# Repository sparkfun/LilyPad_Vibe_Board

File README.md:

LilyPad Vibe Board
=================

[*SparkFun LilyPad Vibe Board (DEV-11008)*](https://www.sparkfun.com/products/11008)

Apply 5V and be shaken by this small, but powerful vibration motor. Works great as an physical indicator without notifying anyone but the wearer. This version uses a surface mount motor which is less likely to be damaged during use. When using with a 3.3V LilyPad Arduino, make sure to use a [transistor](https://www.sparkfun.com/products/11214) in order to source enough current.

Repository Contents
-------------------

* **/Firmware** - Arduino example code
* **/Hardware** - All Eagle design files (.brd, .sch)
* **/Production** - Test bed files and production panel files

Documentation
--------------

* **[LilyPad Vibe Board Hookup Guide](https://learn.sparkfun.com/tutorials/lilypad-vibe-board-hookup-guide)** - The LilyPad Vibe Board is a small vibration motor that can be sewn into projects with conductive thread and controlled by a LilyPad Arduino. The board can be used as a physical indicator on clothing and costumes for haptic feedback.
* **[LilyPad Development Board Activity Guide: Thermal Alert Project](https://learn.sparkfun.com/tutorials/lilypad-development-board-activity-guide/11-thermal-alert-project)** - Example code using LilyPad Temperature Sensor to trigger the LilyPad Vibe Board when a certain temperature is reached.

License Information
-------------------
The hardware is released under [Creative Commons ShareAlike 4.0 International](https://creativecommons.org/licenses/by-sa/4.0/).
The code is beerware; if you see me (or any other SparkFun employee) at the local, and you've found our code helpful, please buy us a round!

Distributed as-is; no warranty is given.

LilyPad is a wearable technology developed by Leah Buechley and cooperatively designed by Leah and SparkFun.
A portion of this sale is given back to Dr. Leah Buechley for continued development and education of e-textiles.

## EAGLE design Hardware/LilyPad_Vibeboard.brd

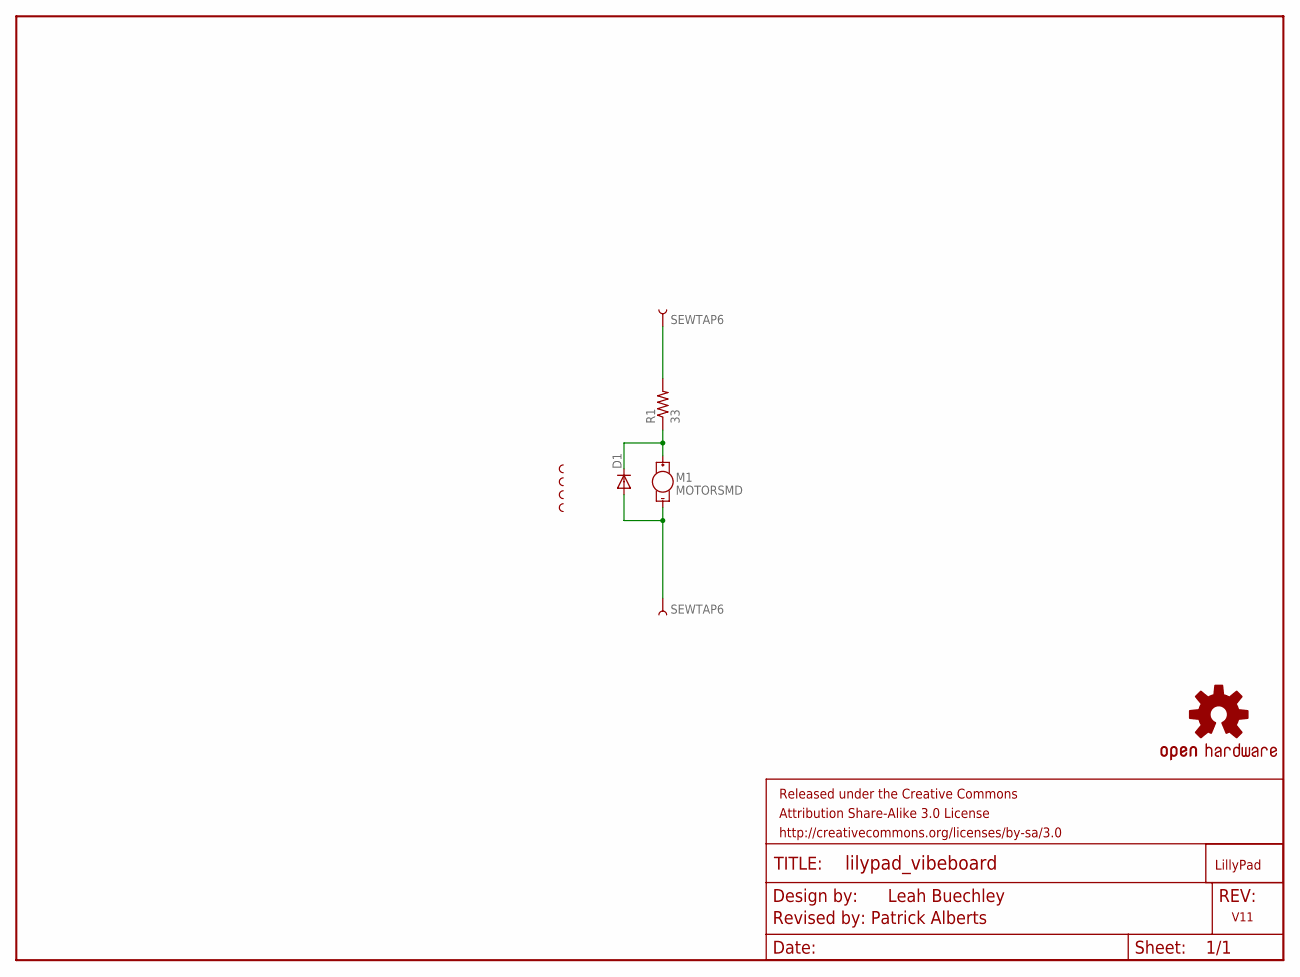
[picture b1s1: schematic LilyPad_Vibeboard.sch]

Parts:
D1: DIODESOD; SOD-323
FRAME1: FRAME-LETTER; CREATIVE_COMMONS
LOGO1: OSHW-LOGOS; OSHW-LOGO-S
M1: MOTORSMD; VIBE-MOTOR-10MM-SMD
R1: 33; 0603-RES
U$2: LOGO-LPLP; LOGO-LILYPAD
VIBE1, VIBE3, VIBE4: SEWTAP-NOHOLE2; PETAL-NOHOLE-2SIDE
VIBE2: SEWTAP-NOHOLEW-MASK; PETAL-NOHOLE-2SIDE-SPECIAL-W-MASK
VIBE+: SEWTAP6; PETAL-SMALL-2SIDE
VIBE-: SEWTAP6; PETAL-SMALL-2SIDE

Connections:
5V: R1.2, VIBE+.1
GND: D1.2 (A), M1.P$2 (-), VIBE-.1
unnamed: D1.1 (C), M1.P$1 (+), R1.1

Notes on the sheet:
Revised by: Patrick Alberts
Leah Buechley
V11

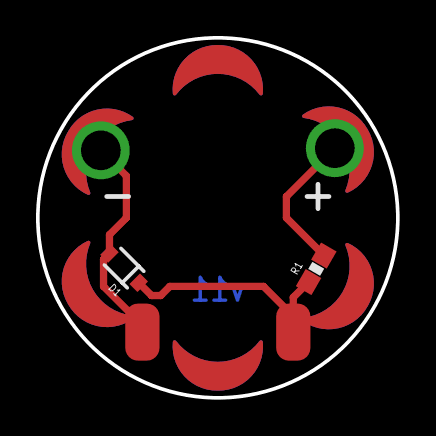
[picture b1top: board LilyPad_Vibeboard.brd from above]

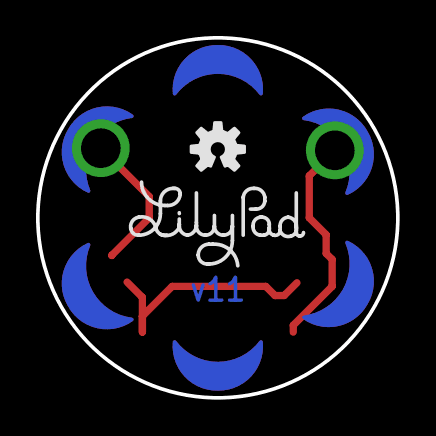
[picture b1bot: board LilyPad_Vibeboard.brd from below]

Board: 2 copper layers, 20.0 x 20.0 mm, 12 parts (2 on the bottom side), 3 nets.

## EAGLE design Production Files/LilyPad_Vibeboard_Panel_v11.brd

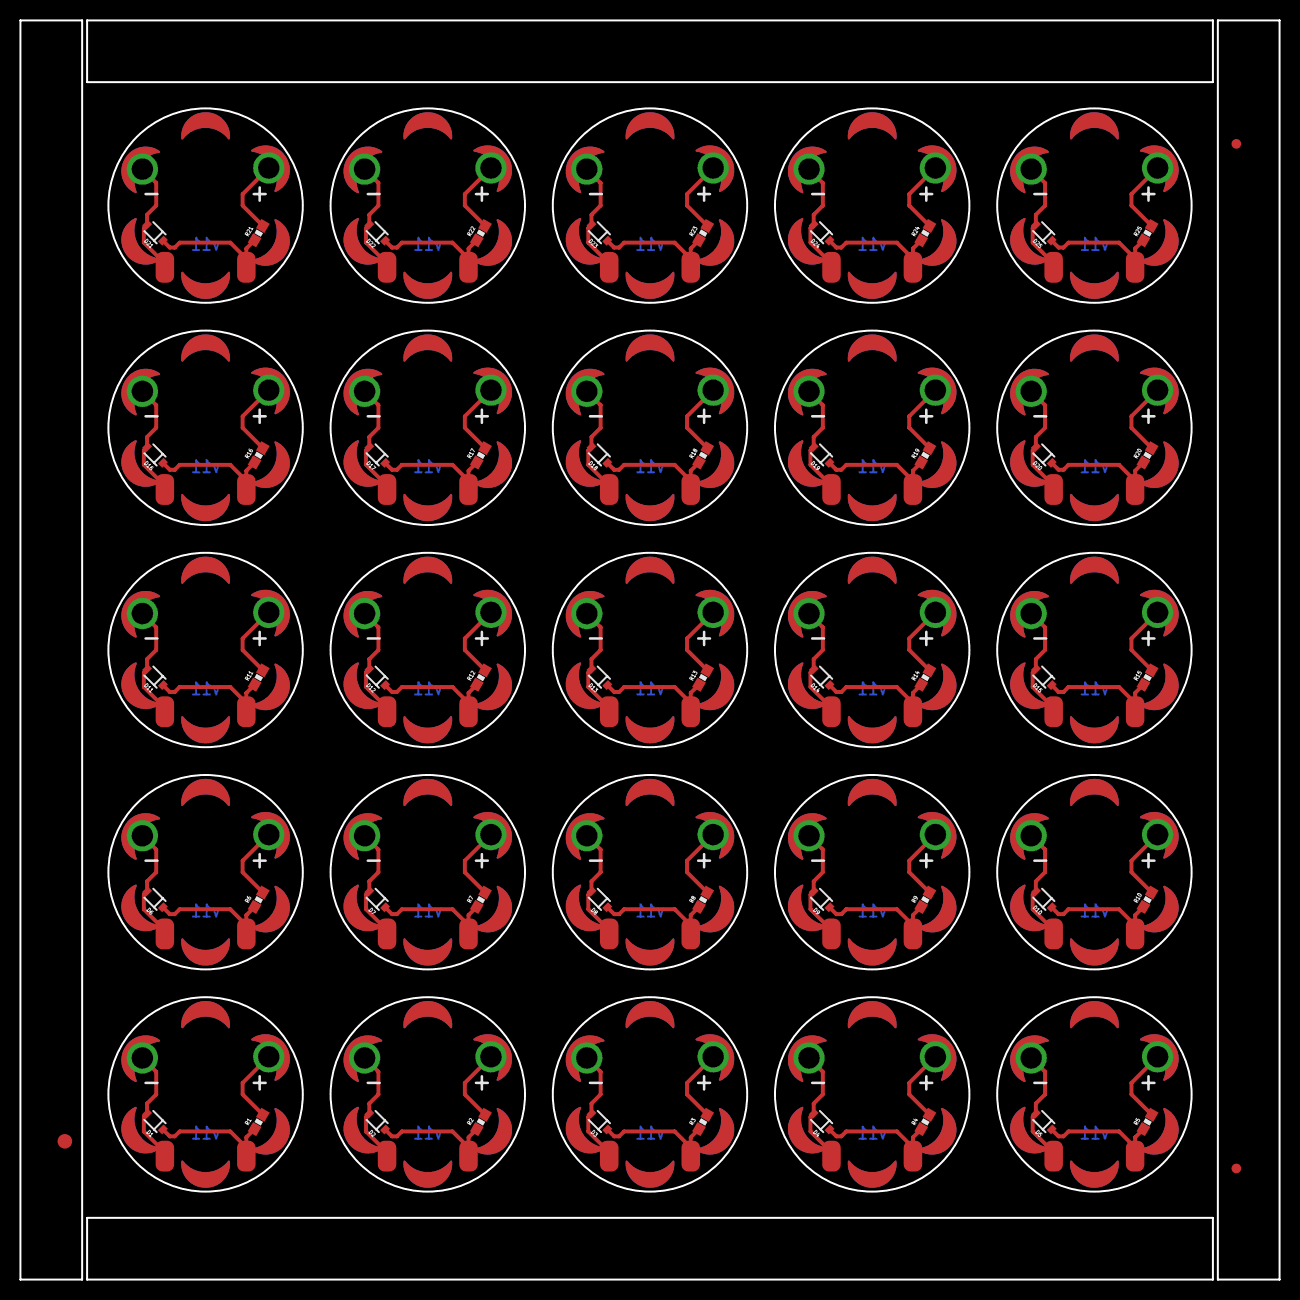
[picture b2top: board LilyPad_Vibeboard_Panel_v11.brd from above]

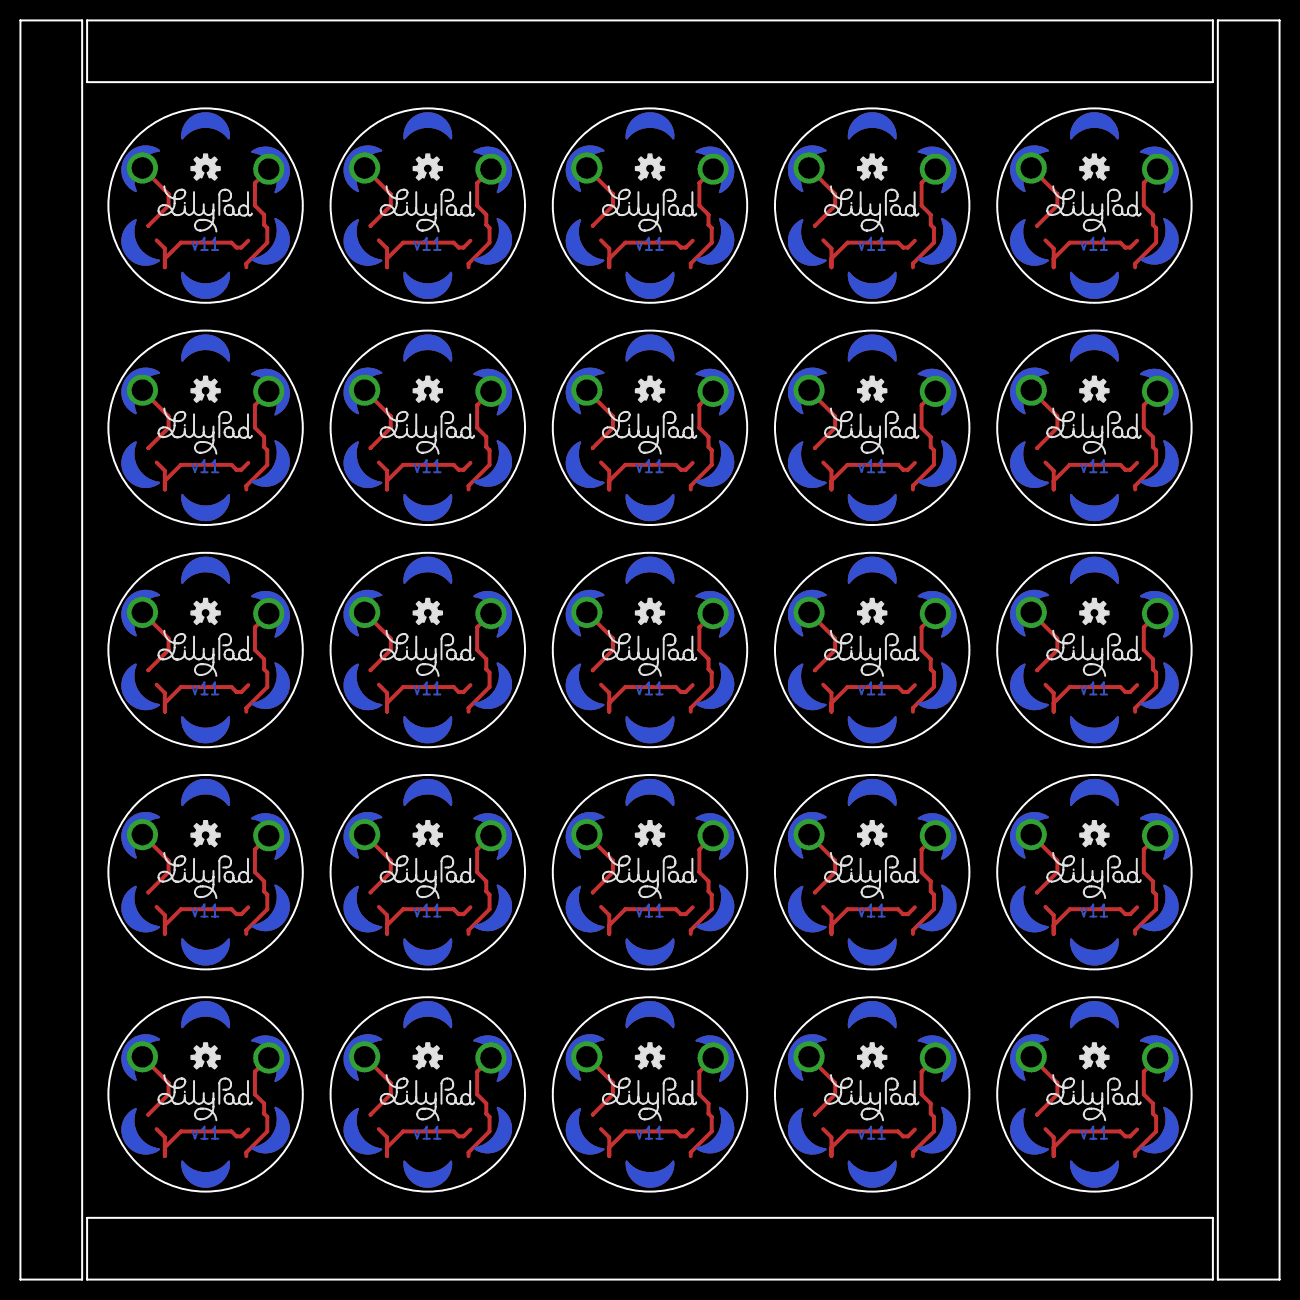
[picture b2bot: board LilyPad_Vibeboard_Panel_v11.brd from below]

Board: 2 copper layers, 129.5 x 129.5 mm, 278 parts (50 on the bottom side), 75 nets.

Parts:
D1, D2, D3, D4, D5, D6, D7, D8, D9, D10, D11, D12, D13, D14, D15, D16, D17, D18, D19, D20, D21, D22, D23, D24, D25: SOD-323
E$1: FIDUCIAL-1.5X3
E$4, E$5: FIDUCIAL-1X2
LOGO1, LOGO2, LOGO3, LOGO4, LOGO5, LOGO6, LOGO7, LOGO8, LOGO9, LOGO10, LOGO11, LOGO12, LOGO13, LOGO14, LOGO15, LOGO16, LOGO17, LOGO18, LOGO19, LOGO20, LOGO21, LOGO22, LOGO23, LOGO24, LOGO25: OSHW-LOGOS; OSHW-LOGO-S
M1, M2, M3, M4, M5, M6, M7, M8, M9, M10, M11, M12, M13, M14, M15, M16, M17, M18, M19, M20, M21, M22, M23, M24, M25: MOTORSMD; VIBE-MOTOR-10MM-SMD
R1, R2, R3, R4, R5, R6, R7, R8, R9, R10, R11, R12, R13, R14, R15, R16, R17, R18, R19, R20, R21, R22, R23, R24, R25: 33; 0603-RES
U$1, U$2, U$3, U$4, U$5, U$6, U$7, U$8, U$9, U$10, U$11, U$12, U$13, U$14, U$15, U$16, U$17, U$18, U$19, U$20, U$21, U$22, U$23, U$24, U$25: LOGO-LPLP; LOGO-LILYPAD
VIBE1, VIBE3, VIBE4, VIBE5, VIBE7, VIBE8, VIBE9, VIBE11, VIBE12, VIBE13, VIBE15, VIBE16, VIBE17, VIBE19, VIBE20, VIBE21, VIBE23, VIBE24, VIBE25, VIBE27, VIBE28, VIBE29, VIBE31, VIBE32, VIBE33, VIBE35, VIBE36, VIBE37, VIBE39, VIBE40, VIBE41, VIBE43, VIBE44, VIBE45, VIBE47, VIBE48, VIBE49, VIBE51, VIBE52, VIBE53, VIBE55, VIBE56, VIBE57, VIBE59, VIBE60, VIBE61, VIBE63, VIBE64, VIBE65, VIBE67, VIBE68, VIBE69, VIBE71, VIBE72, VIBE73, VIBE75, VIBE76, VIBE77, VIBE79, VIBE80, VIBE81, VIBE83, VIBE84, VIBE85, VIBE87, VIBE88, VIBE89, VIBE91, VIBE92, VIBE93, VIBE95, VIBE96, VIBE97, VIBE99, VIBE100: SEWTAP-NOHOLE2; PETAL-NOHOLE-2SIDE
VIBE2, VIBE6, VIBE10, VIBE14, VIBE18, VIBE22, VIBE26, VIBE30, VIBE34, VIBE38, VIBE42, VIBE46, VIBE50, VIBE54, VIBE58, VIBE62, VIBE66, VIBE70, VIBE74, VIBE78, VIBE82, VIBE86, VIBE90, VIBE94, VIBE98: SEWTAP-NOHOLEW-MASK; PETAL-NOHOLE-2SIDE-SPECIAL-W-MASK
VIBE+, VIBE+1, VIBE+2, VIBE+3, VIBE+4, VIBE+5, VIBE+6, VIBE+7, VIBE+8, VIBE+9, VIBE+10, VIBE+11, VIBE+12, VIBE+13, VIBE+14, VIBE+15, VIBE+16, VIBE+17, VIBE+18, VIBE+19, VIBE+20, VIBE+21, VIBE+22, VIBE+23, VIBE+24: SEWTAP6; PETAL-SMALL-2SIDE
VIBE-, VIBE-1, VIBE-2, VIBE-3, VIBE-4, VIBE-5, VIBE-6, VIBE-7, VIBE-8, VIBE-9, VIBE-10, VIBE-11, VIBE-12, VIBE-13, VIBE-14, VIBE-15, VIBE-16, VIBE-17, VIBE-18, VIBE-19, VIBE-20, VIBE-21, VIBE-22, VIBE-23, VIBE-24: SEWTAP6; PETAL-SMALL-2SIDE

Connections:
5V: R1.2, VIBE+.1
5V1: R2.2, VIBE+1.1
5V2: R3.2, VIBE+2.1
5V3: R4.2, VIBE+3.1
5V4: R5.2, VIBE+4.1
5V5: R6.2, VIBE+5.1
5V6: R7.2, VIBE+6.1
5V7: R8.2, VIBE+7.1
5V8: R9.2, VIBE+8.1
5V9: R10.2, VIBE+9.1
5V10: R11.2, VIBE+10.1
5V11: R12.2, VIBE+11.1
5V12: R13.2, VIBE+12.1
5V13: R14.2, VIBE+13.1
5V14: R15.2, VIBE+14.1
5V15: R16.2, VIBE+15.1
5V16: R17.2, VIBE+16.1
5V17: R18.2, VIBE+17.1
5V18: R19.2, VIBE+18.1
5V19: R20.2, VIBE+19.1
5V20: R21.2, VIBE+20.1
5V21: R22.2, VIBE+21.1
5V22: R23.2, VIBE+22.1
5V23: R24.2, VIBE+23.1
5V24: R25.2, VIBE+24.1
GND: D1.2, M1.P$2, VIBE-.1
GND1: D2.2, M2.P$2, VIBE-1.1
GND2: D3.2, M3.P$2, VIBE-2.1
GND3: D4.2, M4.P$2, VIBE-3.1
GND4: D5.2, M5.P$2, VIBE-4.1
GND5: D6.2, M6.P$2, VIBE-5.1
GND6: D7.2, M7.P$2, VIBE-6.1
GND7: D8.2, M8.P$2, VIBE-7.1
GND8: D9.2, M9.P$2, VIBE-8.1
GND9: D10.2, M10.P$2, VIBE-9.1
GND10: D11.2, M11.P$2, VIBE-10.1
GND11: D12.2, M12.P$2, VIBE-11.1
GND12: D13.2, M13.P$2, VIBE-12.1
GND13: D14.2, M14.P$2, VIBE-13.1
GND14: D15.2, M15.P$2, VIBE-14.1
GND15: D16.2, M16.P$2, VIBE-15.1
GND16: D17.2, M17.P$2, VIBE-16.1
GND17: D18.2, M18.P$2, VIBE-17.1
GND18: D19.2, M19.P$2, VIBE-18.1
GND19: D20.2, M20.P$2, VIBE-19.1
GND20: D21.2, M21.P$2, VIBE-20.1
GND21: D22.2, M22.P$2, VIBE-21.1
GND22: D23.2, M23.P$2, VIBE-22.1
GND23: D24.2, M24.P$2, VIBE-23.1
GND24: D25.2, M25.P$2, VIBE-24.1
unnamed: D1.1, M1.P$1, R1.1
unnamed: D2.1, M2.P$1, R2.1
unnamed: D3.1, M3.P$1, R3.1
unnamed: D4.1, M4.P$1, R4.1
unnamed: D5.1, M5.P$1, R5.1
unnamed: D6.1, M6.P$1, R6.1
unnamed: D7.1, M7.P$1, R7.1
unnamed: D8.1, M8.P$1, R8.1
unnamed: D9.1, M9.P$1, R9.1
unnamed: D10.1, M10.P$1, R10.1
unnamed: D11.1, M11.P$1, R11.1
unnamed: D12.1, M12.P$1, R12.1
unnamed: D13.1, M13.P$1, R13.1
unnamed: D14.1, M14.P$1, R14.1
unnamed: D15.1, M15.P$1, R15.1
unnamed: D16.1, M16.P$1, R16.1
unnamed: D17.1, M17.P$1, R17.1
unnamed: D18.1, M18.P$1, R18.1
unnamed: D19.1, M19.P$1, R19.1
unnamed: D20.1, M20.P$1, R20.1
unnamed: D21.1, M21.P$1, R21.1
unnamed: D22.1, M22.P$1, R22.1
unnamed: D23.1, M23.P$1, R23.1
unnamed: D24.1, M24.P$1, R24.1
unnamed: D25.1, M25.P$1, R25.1

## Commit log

2013-09-23 Eagle File Upload
    Upload eagle files and a gitignore
2013-12-09 Moved Traces, Updated to 0603
    Re-routed traces to the tstop does not expose the trace. Also converted
    0402 33K res to 0603.
2013-12-11 Updated Schematic, Trace Routing added OSHW logo
    Updated schematic to "frame letter" re-routed previous traces that did
    not pass the angle check, added OSHW logo.
2014-01-22 Changed Silk
    Moved posi/neg silk marks so that they can be clearly seen.
2014-01-22 Added Version #
2014-01-23 Created Panel
2015-01-19 Updating README to current product page
2019-01-15 Update Button_Feedback.ino
    Add Serial.print()'s for debugging

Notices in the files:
parts and their libraries:
SparkFun-Resistors: Licensing: CC v3.0 Share-Alike You are welcome to use this library for commercial purposes.
SparkFun-Aesthetics: Released under the Creative Commons Attribution Share-Alike 3.0 License
SparkFun-Aesthetics: http://creativecommons.org/licenses/by-sa/3.0
